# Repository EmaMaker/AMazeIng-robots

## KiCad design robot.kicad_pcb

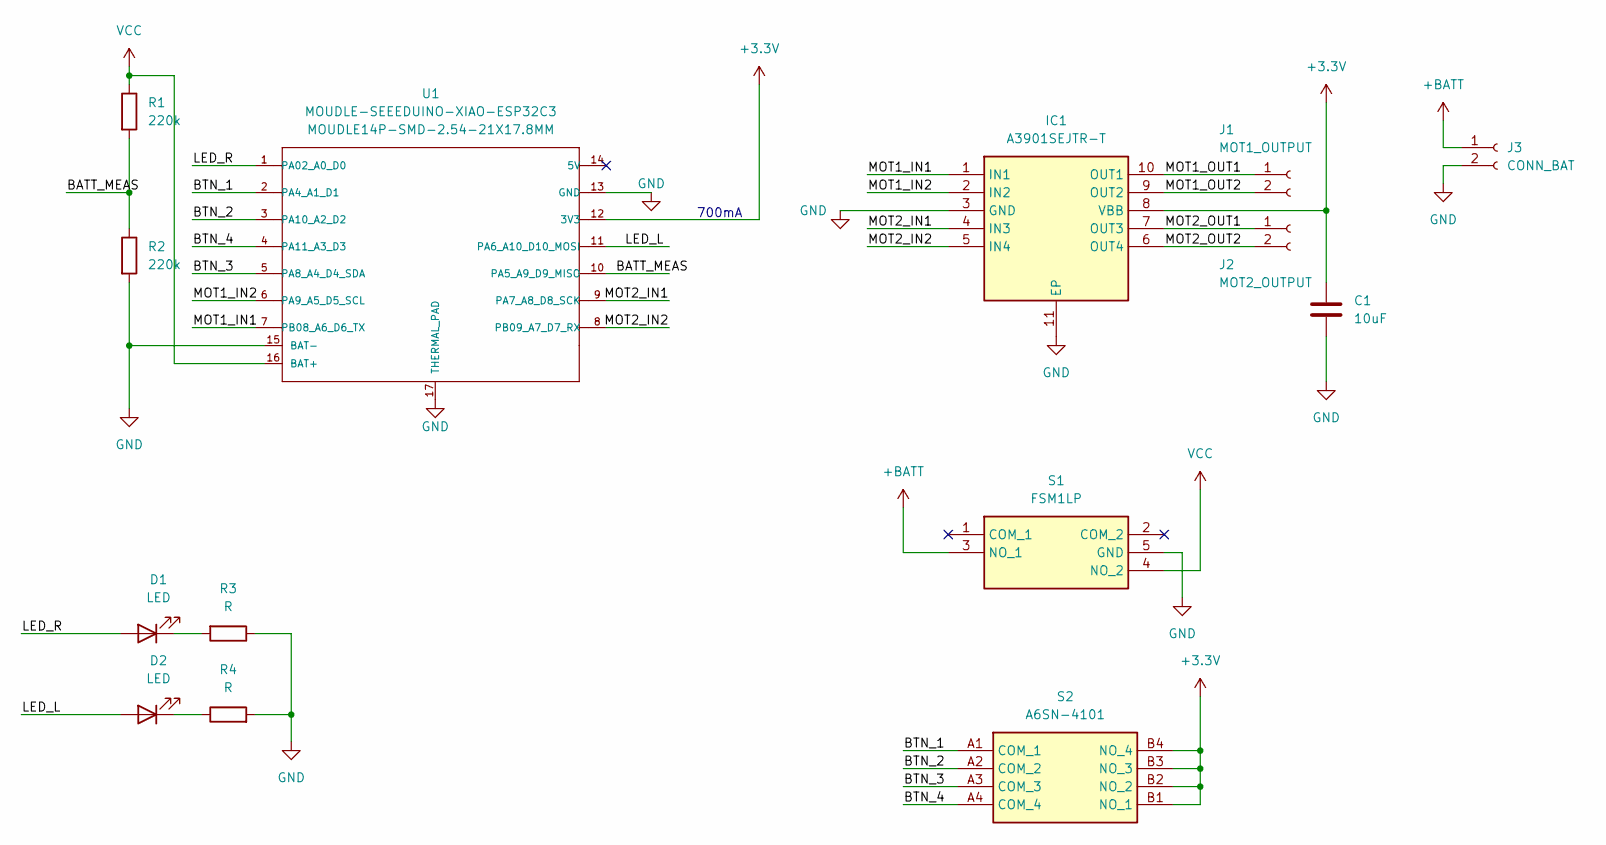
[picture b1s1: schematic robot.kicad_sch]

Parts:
C1: 10uF; C_0603_1608Metric_Pad1.08x0.95mm_HandSolder
D1, D2: LED; LED_0805_2012Metric_Pad1.15x1.40mm_HandSolder
IC1: A3901SEJTR-T; SON50P300X300X75-11N-D; Manufacturer_Part_Number A3901SEJTR-T; Mouser Part Number 250-A3901SEJTR-T
J1: MOT1_OUTPUT; SolderWire-0.1sqmm_1x02_P3.6mm_D0.4mm_OD1mm
J2: MOT2_OUTPUT; SolderWire-0.1sqmm_1x02_P3.6mm_D0.4mm_OD1mm
J3: CONN_BAT; JST_EH_B2B-EH-A_1x02_P2.50mm_Vertical
R1: 220k; C_0603_1608Metric_Pad1.08x0.95mm_HandSolder
R2: 220k; R_0603_1608Metric_Pad0.98x0.95mm_HandSolder
R3, R4: R; R_0603_1608Metric_Pad0.98x0.95mm_HandSolder
S1: FSM1LP; Manufacturer_Part_Number FSM1LP; Mouser Part Number 506-FSM1LP
S2: A6SN-4101; A6SN4101; Manufacturer_Part_Number A6SN-4101; Mouser Part Number 653-A6SN-4101
U1: MOUDLE-SEEEDUINO-XIAO-ESP32C3; MOUDLE14P-SMD-2.54-21X17.8MM

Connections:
+3.3V: C1.1, IC1.8 (VBB), S2.B1 (NO_1), S2.B2 (NO_2), S2.B3 (NO_3), S2.B4 (NO_4), U1.12 (3V3)
+BATT: J3.1, S1.3 (NO_1)
/BATT_MEAS: R1.2, R2.1, U1.10 (PA5_A9_D9_MISO)
/BTN_1: S2.A1 (COM_1), U1.2 (PA4_A1_D1)
/BTN_2: S2.A2 (COM_2), U1.3 (PA10_A2_D2)
/BTN_3: S2.A3 (COM_3), U1.5 (PA8_A4_D4_SDA)
/BTN_4: S2.A4 (COM_4), U1.4 (PA11_A3_D3)
/LED_L: D2.2 (A), U1.11 (PA6_A10_D10_MOSI)
/LED_R: D1.2 (A), U1.1 (PA02_A0_D0)
/MOT1_IN1: IC1.1 (IN1), U1.7 (PB08_A6_D6_TX)
/MOT1_IN2: IC1.2 (IN2), U1.6 (PA9_A5_D5_SCL)
/MOT1_OUT1: IC1.10 (OUT1), J1.1
/MOT1_OUT2: IC1.9 (OUT2), J1.2
/MOT2_IN1: IC1.4 (IN3), U1.9 (PA7_A8_D8_SCK)
/MOT2_IN2: IC1.5 (IN4), U1.8 (PB09_A7_D7_RX)
/MOT2_OUT1: IC1.7 (OUT3), J2.1
/MOT2_OUT2: IC1.6 (OUT4), J2.2
GND: C1.2, IC1.3 (GND), IC1.11 (EP), J3.2, R2.2, R3.1, R4.2, S1.5 (GND), U1.13 (GND), U1.15 (BAT-), U1.17 (THERMAL_PAD)
unnamed: D1.1 (K), R3.2
unnamed: D2.1 (K), R4.1
VCC: R1.1, S1.4 (NO_2), U1.16 (BAT+)

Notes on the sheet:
700mA

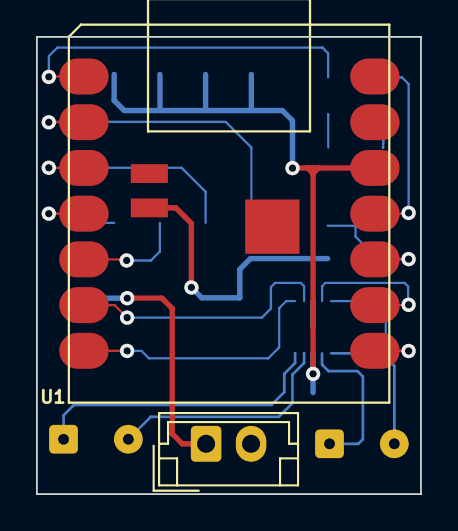
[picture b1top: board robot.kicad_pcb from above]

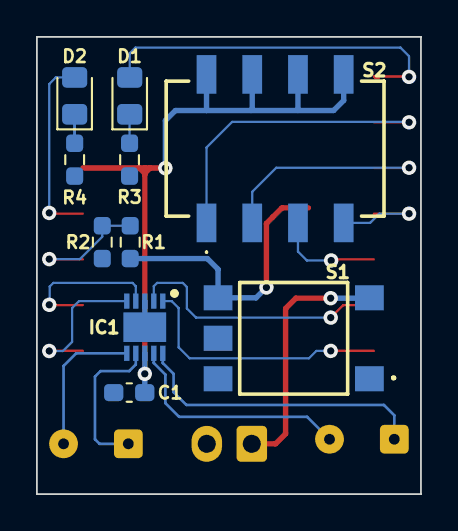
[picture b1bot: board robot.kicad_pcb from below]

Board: 2 copper layers, 21.3 x 25.4 mm, 14 parts (10 on the bottom side), 21 nets.

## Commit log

2024-01-23 add .gitignore
2024-01-23 first routing of the board
2024-01-25 add power switch and battery voltage divider
2024-01-25 6-switch dipswitch for misc. configuration
2024-01-28 jlcpcb drc rules
2024-01-28 4-switch dipswitch, LEDs, reorder
